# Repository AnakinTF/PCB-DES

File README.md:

# PCB-DES
PCB cartuchos DES Amstrad CPC
-
Nuevo diseño con condensador
Utilizando la memoria Flash SST39SF040 con encapsulado TSOP32.

Condensador de 100nf versión SMD 0806.

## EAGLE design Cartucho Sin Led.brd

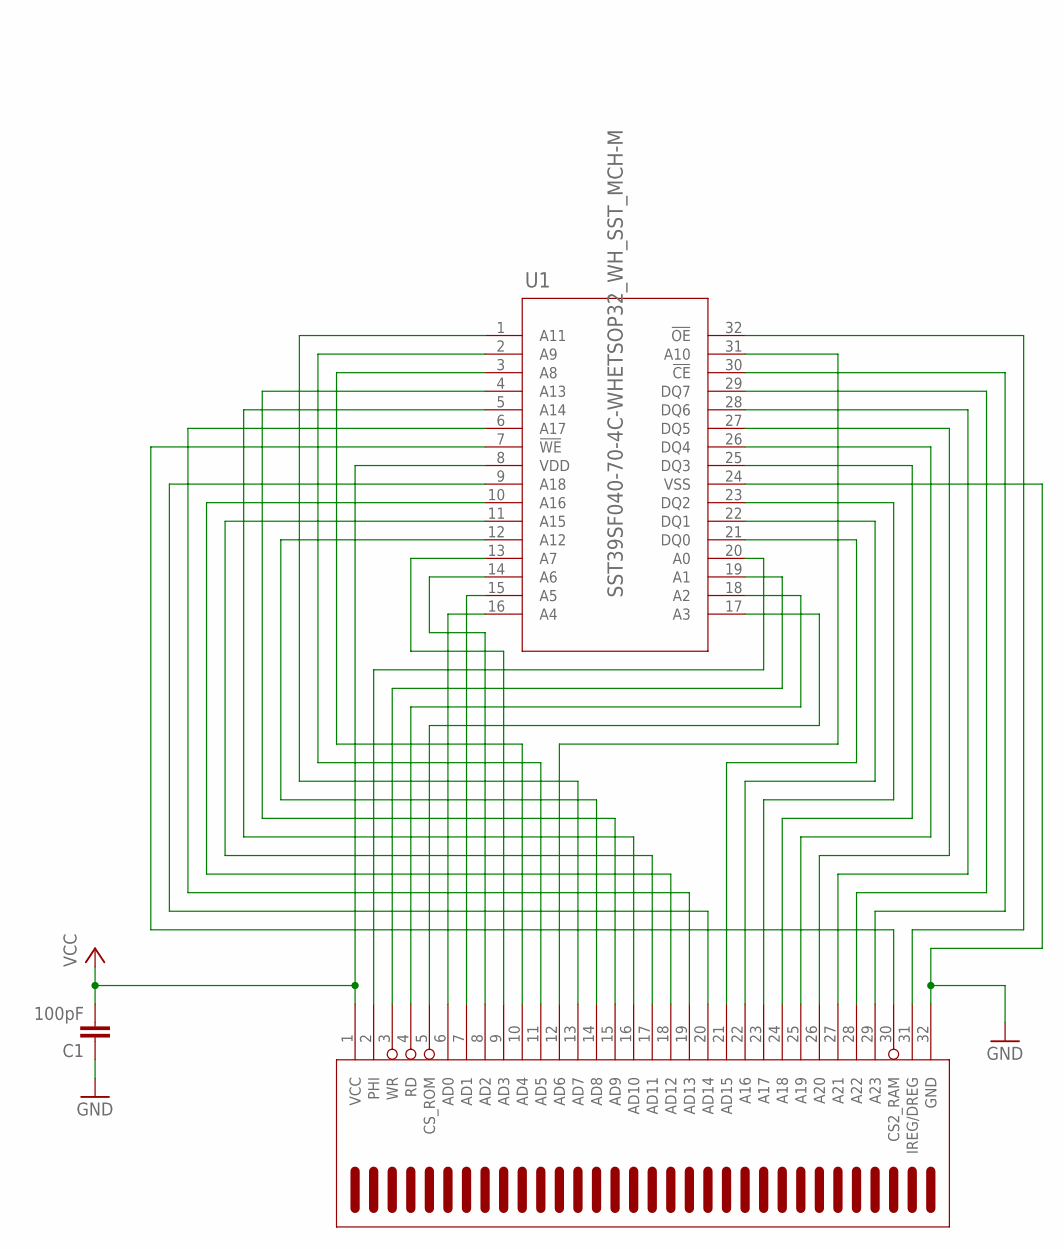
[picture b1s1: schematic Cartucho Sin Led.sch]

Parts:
C1: 100pF; C0805
U1: SST39SF040-70-4C-WHETSOP32_WH_SST_MCH-M; TSOP32_WH_SST_MCH-M
U$1: GBA_CARTNORMAL; GBA_CART

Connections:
GND: C1.1, U1.24 (VSS), U$1.32 (GND)
unnamed: U1.20 (A0), U$1.2 (PHI)
unnamed: U1.19 (A1), U$1.3 (WR)
unnamed: U1.18 (A2), U$1.4 (RD)
unnamed: U1.17 (A3), U$1.5 (CS_ROM)
unnamed: U1.16 (A4), U$1.6 (AD0)
unnamed: U1.15 (A5), U$1.7 (AD1)
unnamed: U1.14 (A6), U$1.8 (AD2)
unnamed: U1.13 (A7), U$1.9 (AD3)
unnamed: U1.3 (A8), U$1.10 (AD4)
unnamed: U1.2 (A9), U$1.11 (AD5)
unnamed: U1.31 (A10), U$1.12 (AD6)
unnamed: U1.1 (A11), U$1.13 (AD7)
unnamed: U1.12 (A12), U$1.14 (AD8)
unnamed: U1.4 (A13), U$1.15 (AD9)
unnamed: U1.5 (A14), U$1.16 (AD10)
unnamed: U1.11 (A15), U$1.17 (AD11)
unnamed: U1.10 (A16), U$1.18 (AD12)
unnamed: U1.6 (A17), U$1.19 (AD13)
unnamed: U1.9 (A18), U$1.20 (AD14)
unnamed: U1.21 (DQ0), U$1.21 (AD15)
unnamed: U1.22 (DQ1), U$1.22 (A16)
unnamed: U1.23 (DQ2), U$1.23 (A17)
unnamed: U1.25 (DQ3), U$1.24 (A18)
unnamed: U1.26 (DQ4), U$1.25 (A19)
unnamed: U1.27 (DQ5), U$1.26 (A20)
unnamed: U1.28 (DQ6), U$1.27 (A21)
unnamed: U1.29 (DQ7), U$1.28 (A22)
unnamed: U1.30 (!CE), U$1.29 (A23)
unnamed: U1.7 (!WE), U$1.30 (CS2_RAM)
unnamed: U1.32 (!OE), U$1.31 (IREG/DREG)
VCC: C1.2, U1.8 (VDD), U$1.1 (VCC)

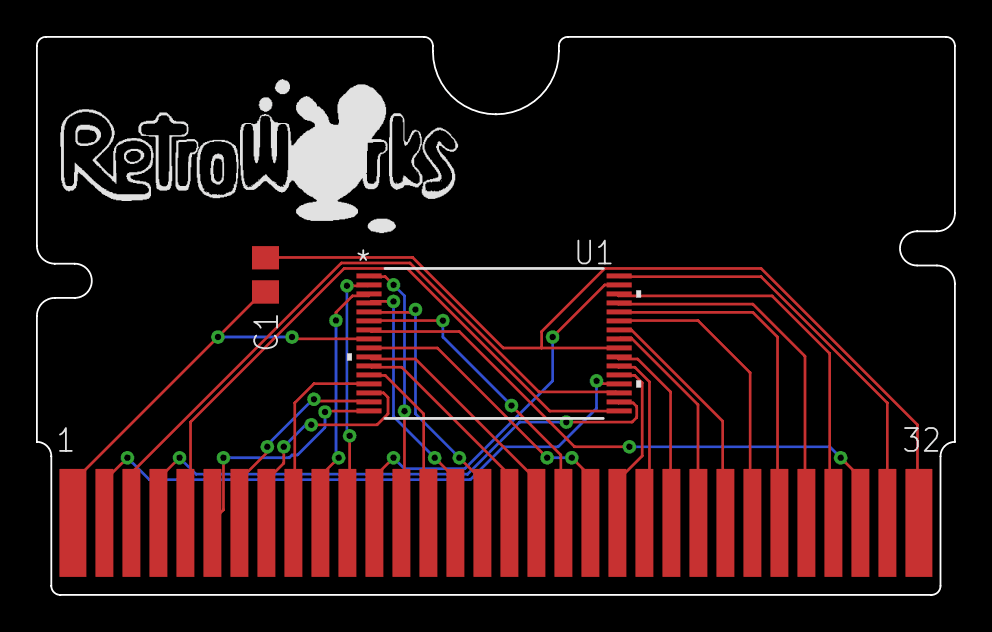
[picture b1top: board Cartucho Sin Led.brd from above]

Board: 2 copper layers, 51.0 x 31.0 mm, 8 parts (1 on the bottom side), 32 nets.

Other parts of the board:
U$2: ANAKINLOGO
U$3: LOGOAMSTRAD20MM
U$4: DES28MM
U$5, U$6: RETROWORKS

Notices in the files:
parts and their libraries:
COPYRIGHT: Copyright (C) 2018 Accelerated Designs. All rights reserved
